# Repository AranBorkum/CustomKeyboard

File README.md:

# Jeremy: A keyboard with a silly name

---

I want to make my own split, low profile custom keyboard. Closely following [this video](https://www.youtube.com/watch?v=7UXsD7nSfDY) I'll try and make a functioning keyboard that works for me

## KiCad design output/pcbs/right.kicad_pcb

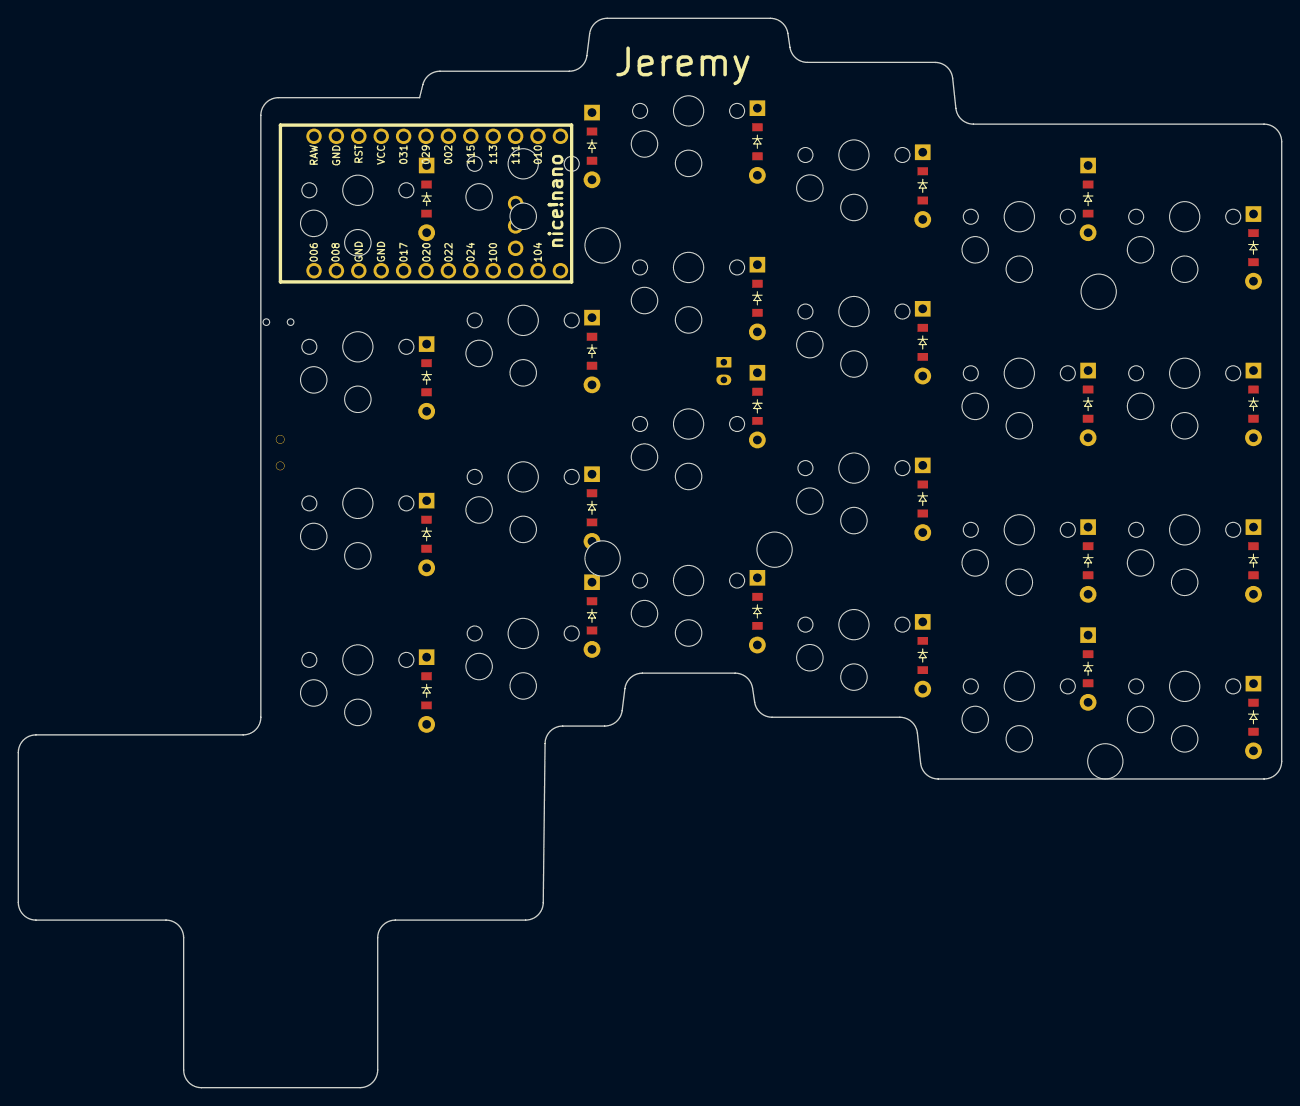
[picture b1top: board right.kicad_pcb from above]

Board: 2 copper layers, 143.2 x 121.3 mm, 52 parts (0 on the bottom side), 38 nets, no tracks yet.

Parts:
B1: Panasonic_EVQPUL_EVQPUC
D1, D2, D3, D4, D5, D6, D7, D8, D9, D10, D11, D12, D13, D14, D15, D16, D17, D18, D19, D20, D21, D22, D23, D24: ComboDiode
JST1: JST_PH_S2B-PH-K_02x2.00mm_Angled
MCU1: nice_nano
S1, S2, S3, S4, S5, S6, S7, S8, S9, S10, S11, S12, S13, S14, S15, S16, S17, S18, S19, S20, S21, S22, S23, S24: PG1350
T1: SPDT_C128955

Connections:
GND: B1.1, JST1.2, MCU1.3, MCU1.4, MCU1.23
P002: D2.1, D5.1, D8.1, D14.1, D17.1, D21.1, MCU1.18
P011: MCU1.10, S17.1, S18.1, S19.1, S20.1
P017: MCU1.5, S21.1, S22.1, S23.1, S24.1
P020: MCU1.6, S1.1, S2.1, S3.1, S4.1
P022: MCU1.7, S5.1, S6.1, S7.1, S8.1
P024: MCU1.8, S9.1, S10.1, S11.1, S12.1
P029: D3.1, D6.1, D9.1, D12.1, D15.1, D18.1, MCU1.19
P031: D4.1, D10.1, D13.1, D20.1, D23.1, D24.1, MCU1.20
P100: MCU1.9, S13.1, S14.1, S15.1, S16.1
P115: D1.1, D7.1, D11.1, D16.1, D19.1, D22.1, MCU1.17
RAW: MCU1.24, T1.2
RST: B1.2, MCU1.22
mirror_fifth_bottom: D22.2, S17.2
mirror_fifth_home: D14.2, S18.2
mirror_fifth_num: D23.2, S20.2
mirror_fifth_top: D15.2, S19.2
mirror_first_bottom: D1.2, S1.2
mirror_first_home: D2.2, S2.2
mirror_first_num: D4.2, S4.2
mirror_first_top: D3.2, S3.2
mirror_fourth_bottom: D11.2, S13.2
mirror_fourth_home: D21.2, S14.2
mirror_fourth_num: D13.2, S16.2
mirror_fourth_top: D12.2, S15.2
mirror_second_bottom: D19.2, S5.2
mirror_second_home: D5.2, S6.2
mirror_second_num: D20.2, S8.2
mirror_second_top: D6.2, S7.2
mirror_sixth_bottom: D16.2, S21.2
mirror_sixth_home: D17.2, S22.2
mirror_sixth_num: D24.2, S24.2
mirror_sixth_top: D18.2, S23.2
mirror_third_bottom: D7.2, S9.2
mirror_third_home: D8.2, S10.2
mirror_third_num: D10.2, S12.2
mirror_third_top: D9.2, S11.2
pos: JST1.1, T1.1

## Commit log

2024-11-19 Add Readme
2024-11-19 Define dependencies
